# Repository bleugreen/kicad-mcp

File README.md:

# KiCad MCP Server

Model Context Protocol (MCP) server for analyzing KiCad printed circuit boards. It
provides a toolkit for PCB analysis, with multi-board schematic signal tracing and
component datasheet lookup, exposed through a simple tool interface.

Single-board schematic text queries (component listings, per-net dumps, single-board
connection tracing) have moved to the companion `kicad-schema` project, which renders a
schematic as structured YAML. This server focuses on the analysis that is still hard to
do in text form: signals that cross board boundaries, datasheet discovery, and the PCB
layout surface that PCB-analysis tooling builds on.

## Features

- **Multi-Board Analysis**: Trace signals across multiple connected boards
- **Datasheet Lookup**: Resolve a manufacturer and part number to a datasheet URL
- **Board & System Configuration**: Register boards and systems; add or remove them without restarting
- **PCB Sources**: Associate a `.kicad_pcb` layout with each board for PCB-analysis tooling
- **PCB Tools (kicad-cli)**: Headless design-rule checking, 3D board renders, and per-layer SVG export from `.kicad_pcb` layouts
- **Live KiCad Session**: Connect to a running KiCad 9 PCB editor through the official IPC API for selection sync and reversible GUI cross-probing
- **Smart Caching**: Optional file caching of parsed schematics for faster repeated queries

## Installation

```bash
# Install with uv (recommended)
uv sync

# Or with pip
pip install -e .
```

**Requirements**: Python 3.10+, and KiCad (for `kicad-cli`). The server discovers
`kicad-cli` automatically at the macOS app-bundle path, `/usr/bin`, and on `PATH`; set
the `KICAD_CLI` environment variable to point at a specific executable.

## Quick Start

### 1. Configure MCP Client

Add to your MCP client configuration (e.g., Claude Desktop's `claude_desktop_config.json`):

```json
{
  "mcpServers": {
    "kicad": {
      "command": "uv",
      "args": [
        "--directory",
        "/path/to/kicad-mcp",
        "run",
        "kicad-mcp"
      ]
    }
  }
}
```

### 2. Create Configuration File

Create `.kicad_mcp.yaml` in your project directory:

```yaml
boards:
  main:
    path: /path/to/main.kicad_sch
    pcb: /path/to/main.kicad_pcb        # optional: PCB layout for PCB-analysis tools
    description: Main controller board

  sensor:
    path: /path/to/sensor.kicad_sch
    description: Sensor board

systems:
  complete:
    boards: [main, sensor]
    description: Full system with all boards

cache:
  enabled: true
  directory: ~/.cache/kicad_mcp
  check_mtime: true
```

## Configuration

Configuration files are searched in priority order:

1. **Environment variable**: `$KICAD_MCP_CONFIG`
2. **Local project**: `.kicad_mcp.yaml` (current directory or parent directories)
3. **Global config**: `~/.config/kicad_mcp/config.yaml`
4. **Default**: Empty configuration (no boards pre-loaded)

### Configuration Options

- **boards**: Named board configurations. Each board has:
  - `path`: path to the `.kicad_sch` schematic file
  - `pcb` *(optional)*: path to the `.kicad_pcb` layout file, used by PCB-analysis tools
  - `description` *(optional)*: human-readable description
- **systems**: Multi-board system definitions referencing board names
- **cache.enabled**: Enable/disable pickle caching of parsed schematics
- **cache.directory**: Where to store cache files
- **cache.check_mtime**: Invalidate cache when source files change

## Available Tools

### Board Management

| Tool | Description |
|------|-------------|
| `list_configured_boards` | List all boards from configuration |
| `list_configured_systems` | List all multi-board systems |
| `load_board` | Load a board by name (with caching) |
| `load_system` | Load a multi-board system |
| `reload_config` | Reload configuration without restarting |

### Configuration Management

| Tool | Description |
|------|-------------|
| `add_board` | Add a new board to configuration (schematic `path`, optional `pcb`) |
| `remove_board` | Remove a board from configuration |
| `add_system` | Add a new multi-board system |
| `remove_system` | Remove a system from configuration |

### Multi-Board Analysis

| Tool | Description |
|------|-------------|
| `get_system_overview` | Overview of a multi-board system |
| `trace_cross_board_signal` | Trace a signal across multiple boards |

### Datasheets

| Tool | Description |
|------|-------------|
| `search_datasheet` | Resolve a manufacturer and part number to a datasheet URL |

### PCB Layout (kicad-cli)

These tools operate on the `.kicad_pcb` layout via KiCad's headless `kicad-cli`.
The `source` argument accepts a configured board name (using its `pcb` path), a
direct path to a `.kicad_pcb`, or a path to a `.kicad_sch` (resolved to its
sibling `.kicad_pcb`).

| Tool | Description |
|------|-------------|
| `pcb_drc` | Run Design Rule Check; returns violations grouped by rule with severities, mm coordinates, totals, and the JSON report path. **Fails closed** — a failed run returns an explicit error, never a false clean pass. Accepts `severity` and `max_violations` filters. |
| `pcb_render` | Render the board in 3D to a PNG, returned as an inline image plus the saved file path. Camera controls: `side`, `zoom`, `rotate`, `pan`, `pivot`, `perspective`, `floor`, `width`, `height`, `quality`, `background`. |
| `pcb_export_layers` | Export one SVG per layer (e.g. `F.Cu,B.Cu,Edge.Cuts`) and return the file paths. `fit` defaults to `board` (board-area only) for downstream cropping. |

The underlying wrappers live in `kicad_mcp.kicad_cli` and are importable as plain
functions, so non-MCP consumers (such as a crop/highlight tool that needs
board-area-fitted per-layer SVGs) can call them directly.

### PCB Layout (parsed model)

These tools read a typed, in-memory model of the `.kicad_pcb` (placement, copper,
stackup, pads, tracks, vias, zones) parsed with the pure-Python `kiutils` library
and cached per `(path, mtime)` — no `kicad-cli` process. Their `source` resolves
through `KiCadMCPConfig.resolve_pcb_source` (a configured board's `pcb` path, a
direct `.kicad_pcb` path, or a `.kicad_sch` sibling). The queryable model lives
in `kicad_mcp.pcb_model`; direct 2D PNG rendering lives in
`kicad_mcp.pcb_rendering`.

| Tool | Description |
|------|-------------|
| `pcb_overview` | Board dimensions, layer/stackup summary, footprint/track/via/zone counts, net count, and top nets by copper element count |
| `pcb_component` | A component's placement (position, side, rotation), footprint id, and pads with their nets |
| `pcb_components_near` | Footprints placed within a radius (mm) of a component, with distances |
| `pcb_net_route` | Routed copper length, layer usage, widths, vias, endpoints, and copper-island connectivity for one net |
| `pcb_diff_pair` | Length and via-count comparison for a differential pair, with pair-name inference for common `_P`/`_N` and `+`/`-` conventions |
| `pcb_net_lengths` | Sorted routed lengths for nets matching a glob or regular expression |
| `pcb_current_capacity` | Pattern-first current-capacity estimates for matched nets, sorted by weakest neck, using IPC-2221 trace current formulas |
| `pcb_impedance_estimate` | Pattern-first or hypothetical trace IPC-2141 impedance estimates, including coupled differential estimates when a matched pair is resolved |
| `pcb_crop` | Inline PNG crop of a component, a net's copper bounds, or an explicit board-coordinate window; returns MCP ImageContent plus the saved path |
| `pcb_highlight_net` | Inline PNG with one net drawn bright over dimmed board copper, including lower-alpha zones; returns MCP ImageContent plus the saved path |

### Electrical estimates — IPC-2221 ampacity and IPC-2141 impedance

`pcb_current_capacity` and `pcb_impedance_estimate` are estimate tools, not
thermal simulation or a field solver. They use the same pattern-first behavior as
`pcb_net_lengths`: a glob or regular expression matches nets and returns a table
across all matches. When exactly one net matches, `pcb_current_capacity` appends
per-segment detail for each `(layer, width)` geometry.

`pcb_current_capacity` estimates each routed track geometry from copper width,
stackup copper thickness, layer type, and requested temperature rise using the
IPC-2221 internal or external trace current formula as appropriate for the layer.
Rows sort ascending by estimated current so the weakest necks are first;
`min_current_a` turns the table into a pass/flag check. Via barrels are estimated
with IPC-2221 using a stated plating assumption.

`pcb_impedance_estimate` reports IPC-2141 closed-form microstrip or stripline
estimates for each matched `(layer, width)` geometry, or for a hypothetical
`width_mm` plus `layer` when iterating toward a target width. If a pattern
resolves to a differential pair by the existing `_P`/`_N` or `+`/`-` conventions,
it derives the same-layer spacing from route geometry and appends a coupled
differential estimate.

Both tools always print assumptions. Missing stackup copper thickness defaults
to 0.035 mm (1 oz), via plating defaults to 25 µm, and missing dielectric
constant defaults to εr 4.4 only when the height can still be derived or is
provided explicitly. For two-layer boards without stackup, impedance uses board
thickness minus two 35 µm copper foils; multilayer boards without dielectric
thickness refuse the affected layer with an explicit message. Nets carried by
zones are flagged because the pour cross-section is not modeled, so the track
neck may not be the true current limit.

### Live KiCad session (IPC API)

These tools talk to a running KiCad 9 PCB editor through KiCad's official
`kicad-python` (`kipy`) IPC client. They are different from the file-based PCB
model tools above: they operate on the user's visible KiCad GUI session and fail
closed when no IPC server is reachable. To use them, enable KiCad's API server in
KiCad Preferences → Plugins, then keep the target PCB open in the PCB editor. The
server attempts KiCad's default IPC socket, or `KICAD_API_SOCKET` when that
environment variable is set, and every IPC call uses a short timeout so the MCP
server does not hang.

The KiCad 9 Python IPC surface exposes open-document discovery, board item
queries, selection read/write, net queries, and item-by-net queries. It does not
expose a typed zoom or pan command in `kicad-python` 0.7.1, so live focus selects
the target footprint or item and reports that view centering is unavailable rather
than fabricating a GUI state.

| Tool | Description |
|------|-------------|
| `kicad_session` | Report whether KiCad IPC is reachable, the KiCad version, the attempted API socket, and open PCB document paths |
| `kicad_focus` | Select a footprint `reference` or a board `position` (`x_mm`, `y_mm`) in the running PCB editor; view centering is reported as unsupported when the IPC client cannot do it |
| `kicad_highlight_net` | Select all selectable copper items on a live board net so KiCad visibly highlights the routed net in the GUI |
| `kicad_get_selection` | Read the user's current GUI selection as references, nets, item types, and item summaries that compose with parsed-model tools such as `pcb_component` and `pcb_net_route` |
| `kicad_open_board` | Resolves a configured board or PCB path through `KiCadMCPConfig.resolve_pcb_source`, then fails closed because KiCad 9's Python IPC client does not expose an open-board command |

## Usage Examples

### Multi-Board Systems

```python
# Load and overview a system
load_system(system_name="complete")
get_system_overview(system_name="complete")

# Trace SPI signal across boards
trace_cross_board_signal(
    system_name="complete",
    signal_net="/MISO",
    start_component="main:U1",
    end_component="sensor:U2"
)
```

### Datasheet Lookup

```python
search_datasheet(
    manufacturer="Texas Instruments",
    part_number="ADS1299IPAGR"
)
```

### Dynamic Configuration

```python
# Add a new board, including its PCB layout
add_board(
    name="power",
    path="/path/to/power.kicad_sch",
    pcb="/path/to/power.kicad_pcb",
    description="Power supply board"
)

# Create a system with it
add_system(
    name="full_system",
    boards=["main", "sensor", "power"],
    description="Complete system with power"
)

# Reload after manual config edits
reload_config()
```

## Development

```bash
# Install with dev dependencies
uv sync --extra dev

# Run tests
uv run pytest

# Lint
uv run ruff check src/
```

## License

MIT

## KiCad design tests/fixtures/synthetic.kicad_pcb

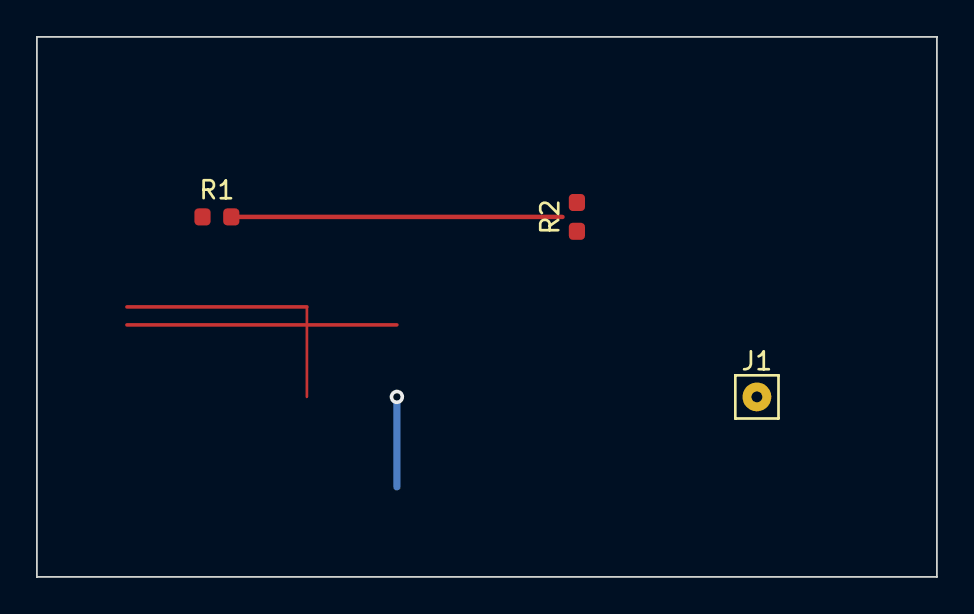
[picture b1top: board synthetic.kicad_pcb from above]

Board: 2 copper layers, 50.0 x 30.0 mm, 4 parts (1 on the bottom side), 3 nets.

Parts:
J1: TH; PinHeader_1x01_P2.54mm_Vertical
R1: 10k; R_0603_1608Metric
R2: 4k7; R_0603_1608Metric
U1: REG; SOT-23

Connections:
GND: J1.1, R2.2, U1.1
SIG: R1.2, R2.1, U1.3
VCC: R1.1, U1.2

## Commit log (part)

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2025-11-14 updated ignore
2025-11-14 init
2025-11-14 Improve README with comprehensive documentation
    - Add clear installation instructions with uv and pip options
    - Include MCP client configuration example for Claude Desktop
    - Organize all 19 tools into logical categories with descriptions
    - Add practical usage examples for common workflows
    - Document configuration file search priority and options
    - Explain source parameter flexibility (board name or file path)
2025-11-14 cleaning up
2025-11-14 added datasheet lookup to examine_component
